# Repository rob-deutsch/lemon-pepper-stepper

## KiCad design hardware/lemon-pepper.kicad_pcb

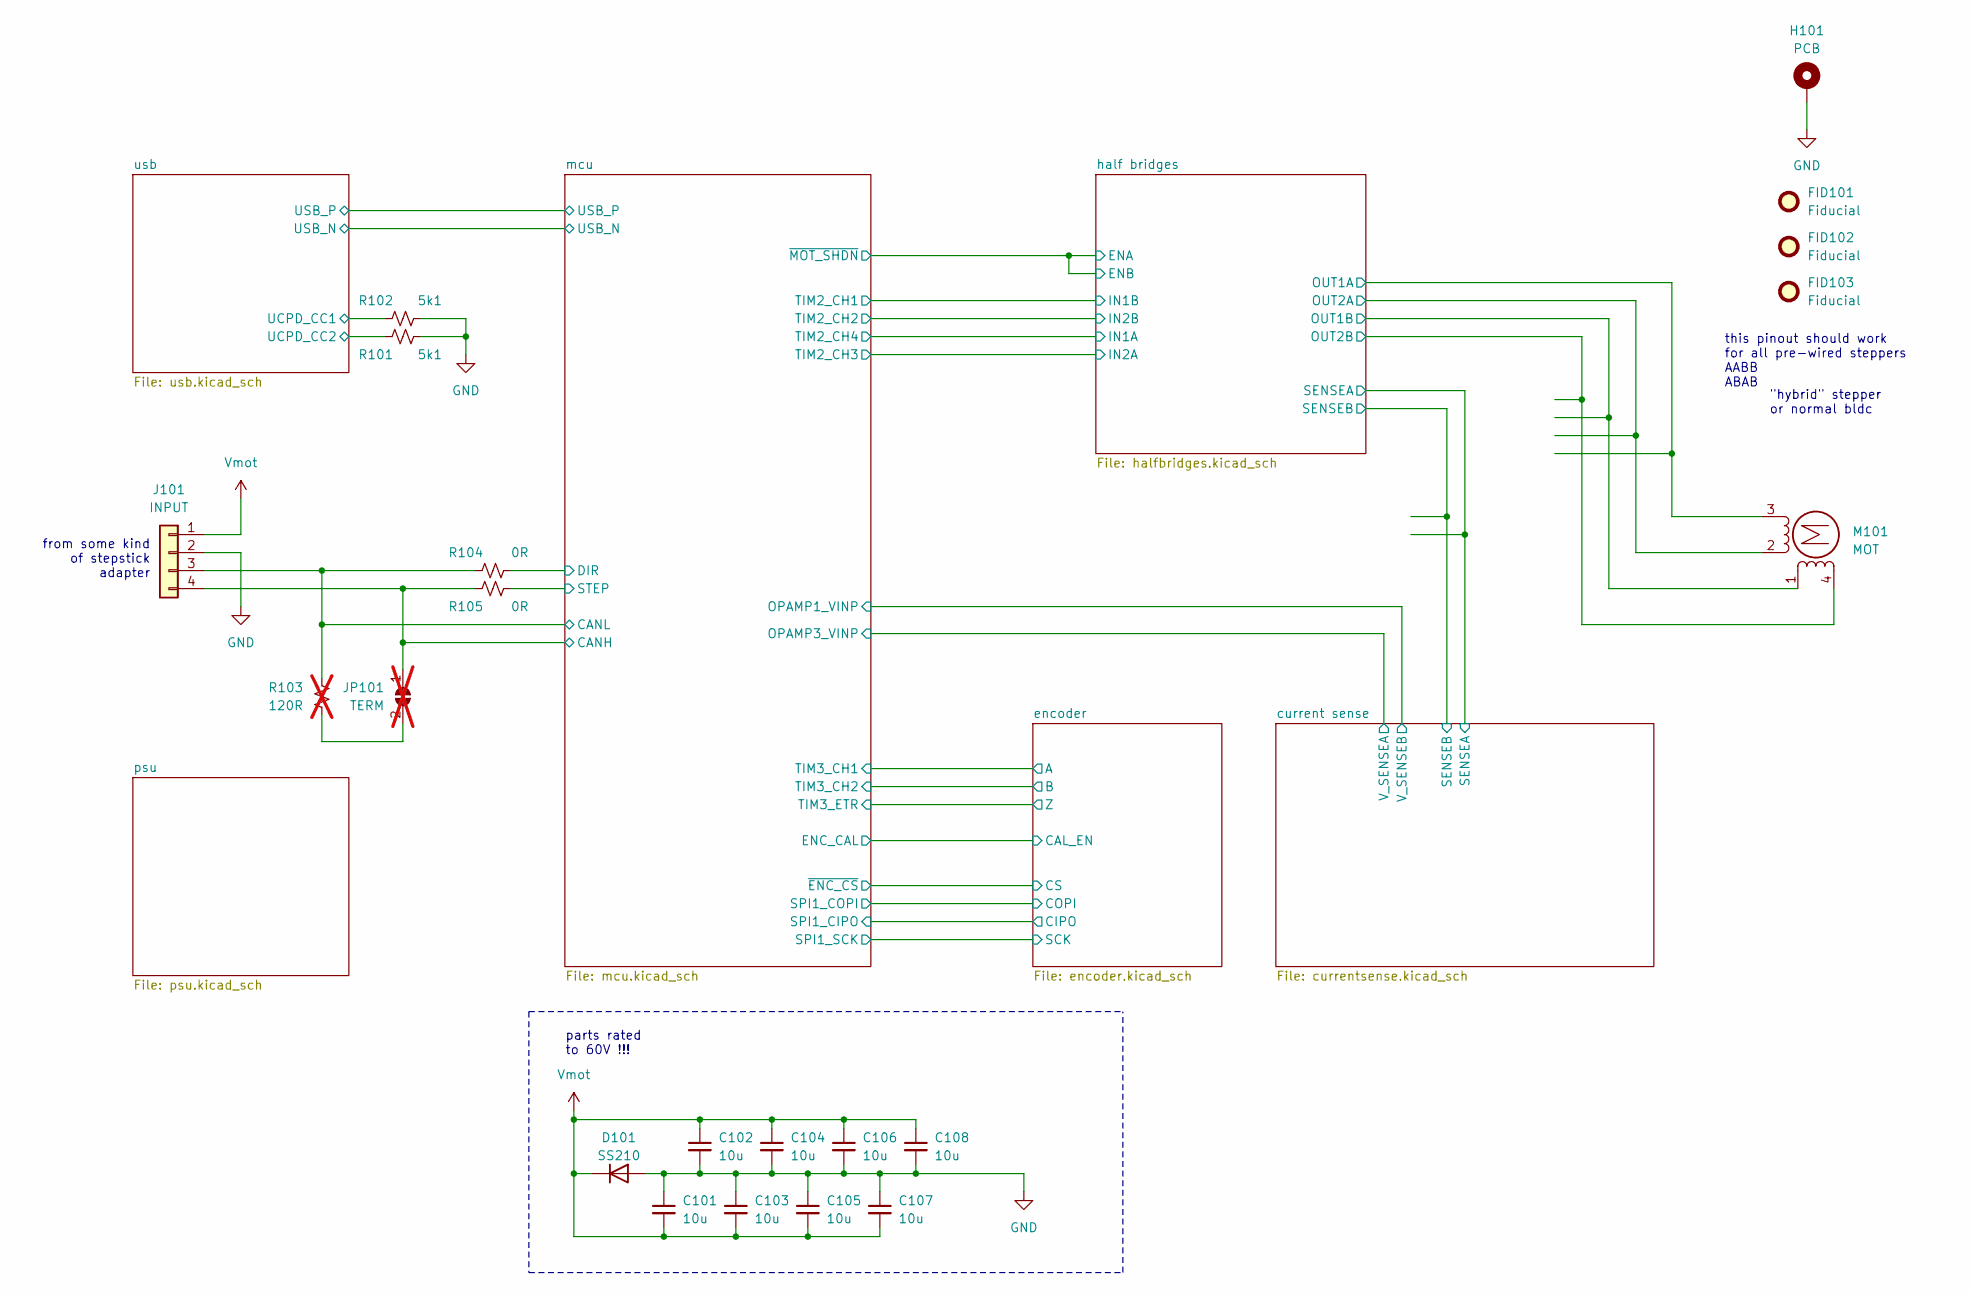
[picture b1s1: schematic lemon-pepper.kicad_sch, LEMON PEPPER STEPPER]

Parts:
C101, C102, C103, C104, C105, C106, C107, C108: 10u; C_0805_2012Metric; LCSC ID C440198
D101: SS210; D_SMA; LCSC ID C14996
FID101, FID102, FID103: Fiducial; Fiducial_0.5mm_Mask1mm
H101: PCB; NEMA17
J101: INPUT; JST_XH_B4B-XH-A_1x04_P2.50mm_Vertical
JP101: TERM; R_0402_1005Metric; not fitted
M101: MOT; XH2.54 4P
R101, R102: 5k1; R_0402_1005Metric; LCSC ID C25905
R103: 120R; R_0402_1005Metric; LCSC ID C25079; not fitted
R104, R105: 0R; R_0402_1005Metric; LCSC ID C17168

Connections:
/CANH: J101.4, JP101.1 (A), R105.2
/CANL: J101.3, R103.1, R104.1
/half bridges/OUT1A: M101.3; also elsewhere on the board
/half bridges/OUT1B: M101.1; also elsewhere on the board
/half bridges/OUT2A: M101.2 (-); also elsewhere on the board
/half bridges/OUT2B: M101.4; also elsewhere on the board
/mcu/DIR: R104.2; also elsewhere on the board
/mcu/STEP: R105.1; also elsewhere on the board
/usb/UCPD_CC1: R102.1; also elsewhere on the board
/usb/UCPD_CC2: R101.2; also elsewhere on the board
GND: C101.1, C102.2, C103.1, C104.2, C105.1, C106.2, C107.1, C108.2, D101.2 (A), H101.1, J101.2, R101.1, R102.2; also elsewhere on the board
unnamed: JP101.2 (B), R103.2
Vmot: C101.2, C102.1, C103.2, C104.1, C105.2, C106.1, C107.2, C108.1, D101.1 (K), J101.1; also elsewhere on the board

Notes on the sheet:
this pinout should work for all pre-wired steppers AABB ABAB
parts rated to 60V !!!
from some kind of stepstick adapter
"hybrid" stepper or normal bldc

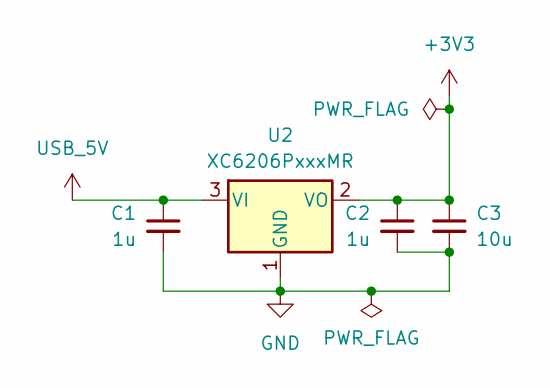
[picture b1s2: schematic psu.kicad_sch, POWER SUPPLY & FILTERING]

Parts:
C1, C2: 1u; C_0402_1005Metric; LCSC ID C52923
C3: 10u; C_0805_2012Metric; LCSC ID C440198
U2: XC6206PxxxMR; SOT-23-3; LCSC ID C5446

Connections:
+3V3: C2.1, C3.1, U2.2 (VO); also elsewhere on the board
GND: C1.2, C2.2, C3.2, U2.1 (GND); also elsewhere on the board
USB_5V: C1.1, U2.3 (VI); also elsewhere on the board

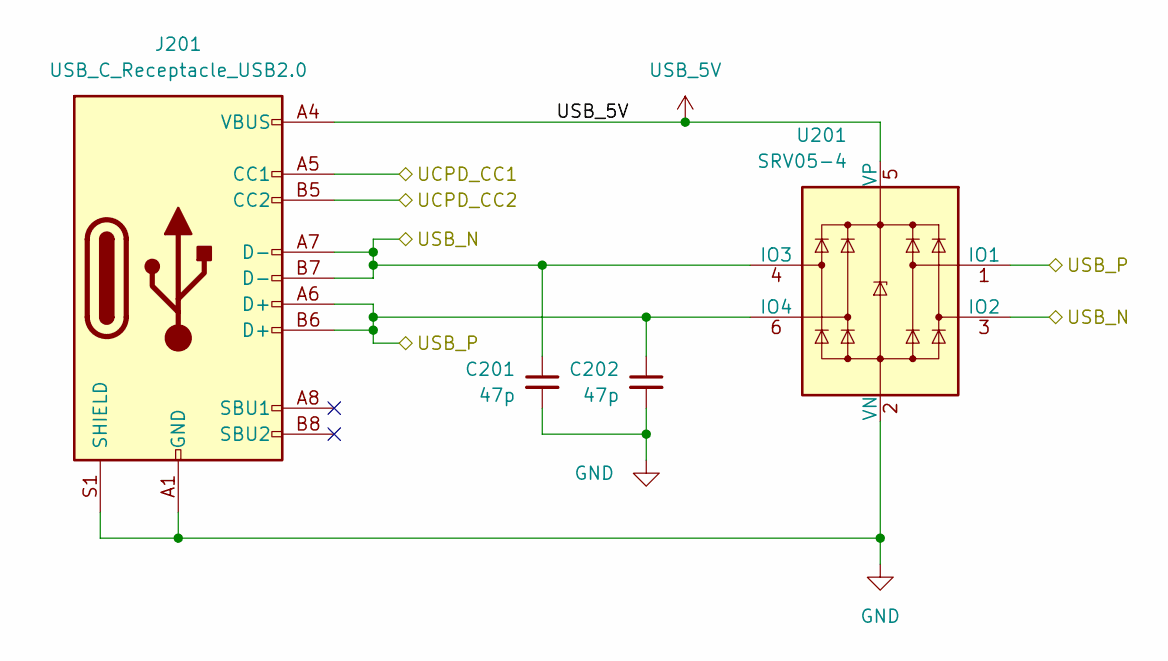
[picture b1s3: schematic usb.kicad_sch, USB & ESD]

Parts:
C201, C202: 47p; C_0402_1005Metric; LCSC ID C1567
J201: USB_C_Receptacle_USB2.0; usb_c; LCSC ID C963223
U201: SRV05-4; SOT-23-6; LCSC ID C7420376

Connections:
/mcu/USBD_N: C201.1, J201.A7 (D-), J201.B7 (D-), U201.3 (IO2), U201.4 (IO3); also elsewhere on the board
/mcu/USBD_P: C202.1, J201.A6 (D+), J201.B6 (D+), U201.1 (IO1), U201.6 (IO4); also elsewhere on the board
/usb/UCPD_CC1: J201.A5 (CC1); also elsewhere on the board
/usb/UCPD_CC2: J201.B5 (CC2); also elsewhere on the board
GND: C201.2, C202.2, J201.A1 (GND), J201.A12 (GND), J201.B1 (GND), J201.B12 (GND), J201.S1 (SHIELD), U201.2 (VN); also elsewhere on the board
USB_5V: J201.A4 (VBUS), J201.A9 (VBUS), J201.B4 (VBUS), J201.B9 (VBUS), U201.5 (VP); also elsewhere on the board

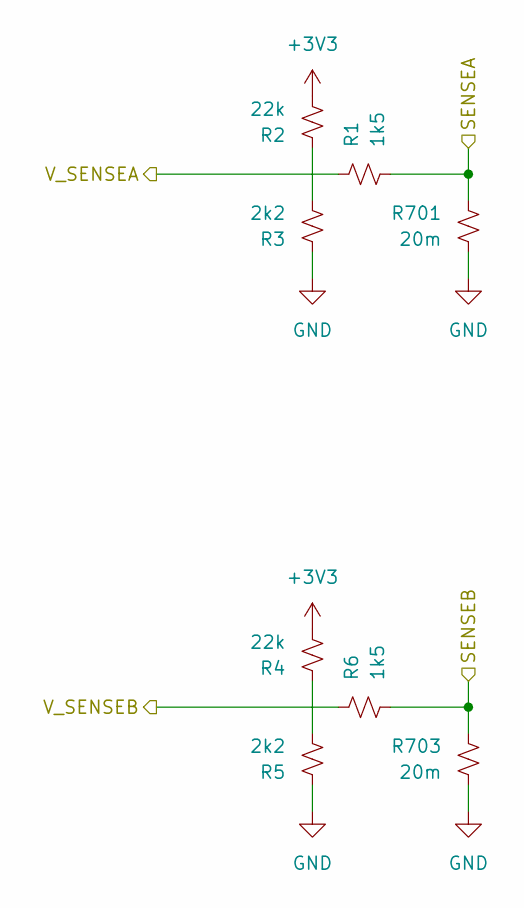
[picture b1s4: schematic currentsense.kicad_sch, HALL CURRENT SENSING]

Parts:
R1, R6: 1k5; R_0402_1005Metric; LCSC ID C25867
R2, R4: 22k; R_0402_1005Metric
R3, R5: 2k2; R_0402_1005Metric
R701, R703: 20m; R_1206_3216Metric; LCSC ID C393094

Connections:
+3V3: R2.2, R4.2; also elsewhere on the board
/current sense/SENSEA: R1.2, R701.1; also elsewhere on the board
/current sense/SENSEB: R6.2, R703.1; also elsewhere on the board
/current sense/V_SENSEA: R1.1; also elsewhere on the board
/current sense/V_SENSEB: R6.1; also elsewhere on the board
GND: R3.1, R5.1, R701.2, R703.2; also elsewhere on the board
unnamed: R2.1, R3.2
unnamed: R4.1, R5.2

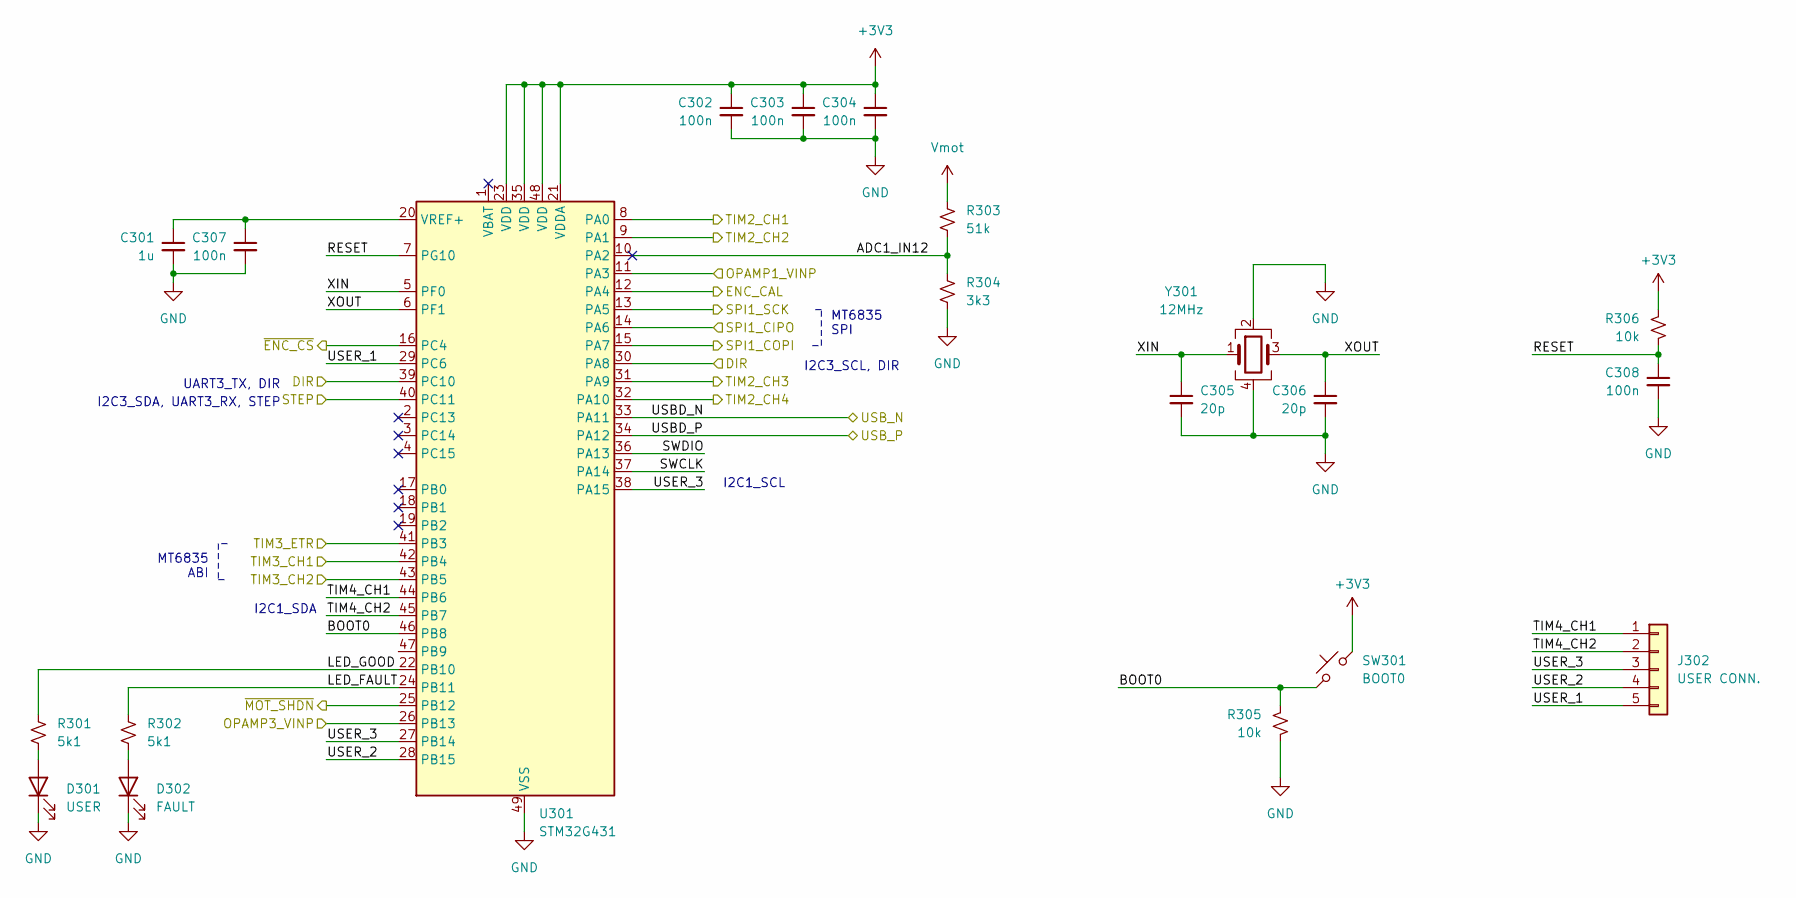
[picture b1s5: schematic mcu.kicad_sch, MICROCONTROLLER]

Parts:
C301: 1u; C_0402_1005Metric; LCSC ID C52923
C302, C303, C304, C307, C308: 100n; C_0402_1005Metric; LCSC ID C307331
C305, C306: 20p; C_0402_1005Metric; LCSC ID C1554
D301: USER; D_0603_1608Metric; LCSC ID C72041
D302: FAULT; D_0603_1608Metric; LCSC ID C2286
J302: USER CONN.; PinHeader_1x05_P1.27mm_SMD
R301, R302: 5k1; R_0402_1005Metric; LCSC ID C25905
R303: 51k; R_0402_1005Metric; LCSC ID C25794
R304: 3k3; R_0402_1005Metric; LCSC ID C25890
R305, R306: 10k; R_0402_1005Metric; LCSC ID C25744
SW301: BOOT0; SW_SPST_B3U-3000P; LCSC ID C963349
U301: STM32G431; QFN-48-1EP_7x7mm_P0.5mm_EP5.6x5.6mm; LCSC ID C529356
Y301: 12MHz; Crystal_SMD_3225-4Pin_3.2x2.5mm; LCSC ID C9002

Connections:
+3V3: C302.1, C303.1, C304.1, R306.1, SW301.2, U301.21 (VDDA), U301.23 (VDD), U301.35 (VDD), U301.48 (VDD); also elsewhere on the board
/current sense/V_SENSEA: U301.26 (PB13); also elsewhere on the board
/current sense/V_SENSEB: U301.11 (PA3); also elsewhere on the board
/encoder/A: U301.42 (PB4); also elsewhere on the board
/encoder/B: U301.43 (PB5); also elsewhere on the board
/encoder/CAL_EN: U301.12 (PA4); also elsewhere on the board
/encoder/CIPO: U301.14 (PA6); also elsewhere on the board
/encoder/COPI: U301.15 (PA7); also elsewhere on the board
/encoder/CS: U301.16 (PC4); also elsewhere on the board
/encoder/SCK: U301.13 (PA5); also elsewhere on the board
/encoder/Z: U301.41 (PB3); also elsewhere on the board
/half bridges/ENA: U301.25 (PB12); also elsewhere on the board
/half bridges/IN1A: U301.32 (PA10); also elsewhere on the board
/half bridges/IN1B: U301.8 (PA0); also elsewhere on the board
/half bridges/IN2A: U301.31 (PA9); also elsewhere on the board
/half bridges/IN2B: U301.9 (PA1); also elsewhere on the board
/mcu/ADC1_IN12: R303.2, R304.1, U301.10 (PA2)
/mcu/BOOT0: R305.1, SW301.1, U301.46 (PB8)
/mcu/DIR: U301.30 (PA8), U301.39 (PC10); also elsewhere on the board
/mcu/LED_FAULT: R302.1, U301.24 (PB11)
/mcu/LED_GOOD: R301.1, U301.22 (PB10)
/mcu/RESET: C308.1, R306.2, U301.7 (PG10); also elsewhere on the board
/mcu/STEP: U301.40 (PC11); also elsewhere on the board
/mcu/SWCLK: U301.37 (PA14); also elsewhere on the board
/mcu/SWDIO: U301.36 (PA13); also elsewhere on the board
/mcu/TIM4_CH1: J302.1, U301.44 (PB6)
/mcu/TIM4_CH2: J302.2, U301.45 (PB7)
/mcu/USBD_N: U301.33 (PA11); also elsewhere on the board
/mcu/USBD_P: U301.34 (PA12); also elsewhere on the board
/mcu/USER_1: J302.5, U301.29 (PC6)
/mcu/USER_2: J302.4, U301.28 (PB15)
/mcu/USER_3: J302.3, U301.27 (PB14), U301.38 (PA15)
/mcu/XIN: C305.1, U301.5 (PF0), Y301.1
/mcu/XOUT: C306.1, U301.6 (PF1), Y301.3
GND: C301.2, C302.2, C303.2, C304.2, C305.2, C306.2, C307.2, C308.2, D301.1 (K), D302.1 (K), R304.2, R305.2, U301.49 (VSS), Y301.2, Y301.4; also elsewhere on the board
unnamed: D301.2 (A), R301.2
unnamed: D302.2 (A), R302.2
unnamed: C301.1, C307.1, U301.20 (VREF+)
Vmot: R303.1; also elsewhere on the board

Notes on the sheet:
MT6835 ABI
I2C3_SDA, UART3_RX, STEP
I2C1_SDA
I2C1_SCL
MT6835 SPI
I2C3_SCL, DIR
UART3_TX, DIR

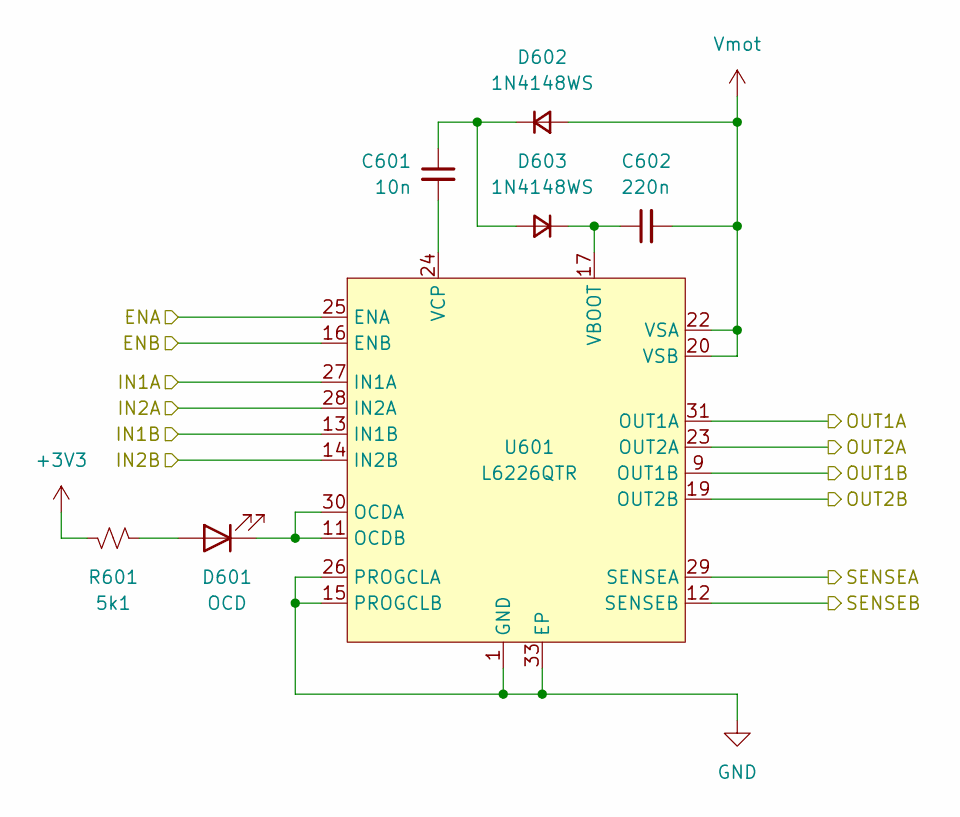
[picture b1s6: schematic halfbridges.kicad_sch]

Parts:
C601: 10n; C_0402_1005Metric; LCSC ID C15195
C602: 220n; C_0402_1005Metric; LCSC ID C16772
D601: OCD; D_0603_1608Metric; LCSC ID C2286
D602, D603: 1N4148WS; D_SOD-323; LCSC ID C81598
R601: 5k1; R_0402_1005Metric; LCSC ID C25905
U601: L6226QTR; ST-L6226Q-VQFN32; LCSC ID C95357

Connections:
+3V3: R601.2; also elsewhere on the board
/current sense/SENSEA: U601.29 (SENSEA); also elsewhere on the board
/current sense/SENSEB: U601.12 (SENSEB); also elsewhere on the board
/half bridges/ENA: U601.16 (ENB), U601.25 (ENA); also elsewhere on the board
/half bridges/IN1A: U601.27 (IN1A); also elsewhere on the board
/half bridges/IN1B: U601.13 (IN1B); also elsewhere on the board
/half bridges/IN2A: U601.28 (IN2A); also elsewhere on the board
/half bridges/IN2B: U601.14 (IN2B); also elsewhere on the board
/half bridges/OUT1A: U601.31 (OUT1A); also elsewhere on the board
/half bridges/OUT1B: U601.9 (OUT1B); also elsewhere on the board
/half bridges/OUT2A: U601.23 (OUT2A); also elsewhere on the board
/half bridges/OUT2B: U601.19 (OUT2B); also elsewhere on the board
GND: U601.1 (GND), U601.2 (NC), U601.3 (NC), U601.4 (NC), U601.5 (NC), U601.6 (NC), U601.7 (NC), U601.8 (NC), U601.15 (PROGCLB), U601.21 (GND), U601.26 (PROGCLA), U601.33 (EP); also elsewhere on the board
unnamed: D601.2 (A), R601.1
unnamed: D601.1 (K), U601.11 (OCDB), U601.30 (OCDA)
unnamed: C601.1, D602.1 (K), D603.2 (A)
unnamed: C602.1, D603.1 (K), U601.17 (VBOOT)
unnamed: C601.2, U601.24 (VCP)
Vmot: C602.2, D602.2 (A), U601.20 (VSB), U601.22 (VSA); also elsewhere on the board

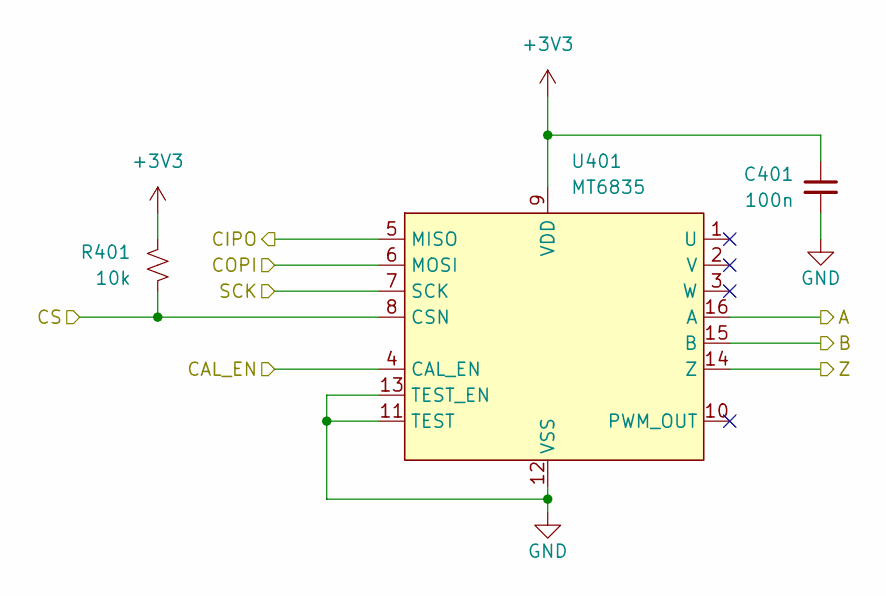
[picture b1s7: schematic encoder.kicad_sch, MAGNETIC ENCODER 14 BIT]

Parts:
C401: 100n; C_0402_1005Metric; LCSC ID C307331
R401: 10k; R_0402_1005Metric; LCSC ID C25744
U401: MT6835; MagnTek TSSOP-16-1EP_4.4x5mm_P0.65mm; LCSC ID C2932578

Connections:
+3V3: C401.1, R401.1, U401.9 (VDD); also elsewhere on the board
/encoder/A: U401.16 (A); also elsewhere on the board
/encoder/B: U401.15 (B); also elsewhere on the board
/encoder/CAL_EN: U401.4 (CAL_EN); also elsewhere on the board
/encoder/CIPO: U401.5 (MISO); also elsewhere on the board
/encoder/COPI: U401.6 (MOSI); also elsewhere on the board
/encoder/CS: R401.2, U401.8 (CSN); also elsewhere on the board
/encoder/SCK: U401.7 (SCK); also elsewhere on the board
/encoder/Z: U401.14 (Z); also elsewhere on the board
GND: C401.2, U401.11 (TEST), U401.12 (VSS), U401.13 (TEST_EN); also elsewhere on the board

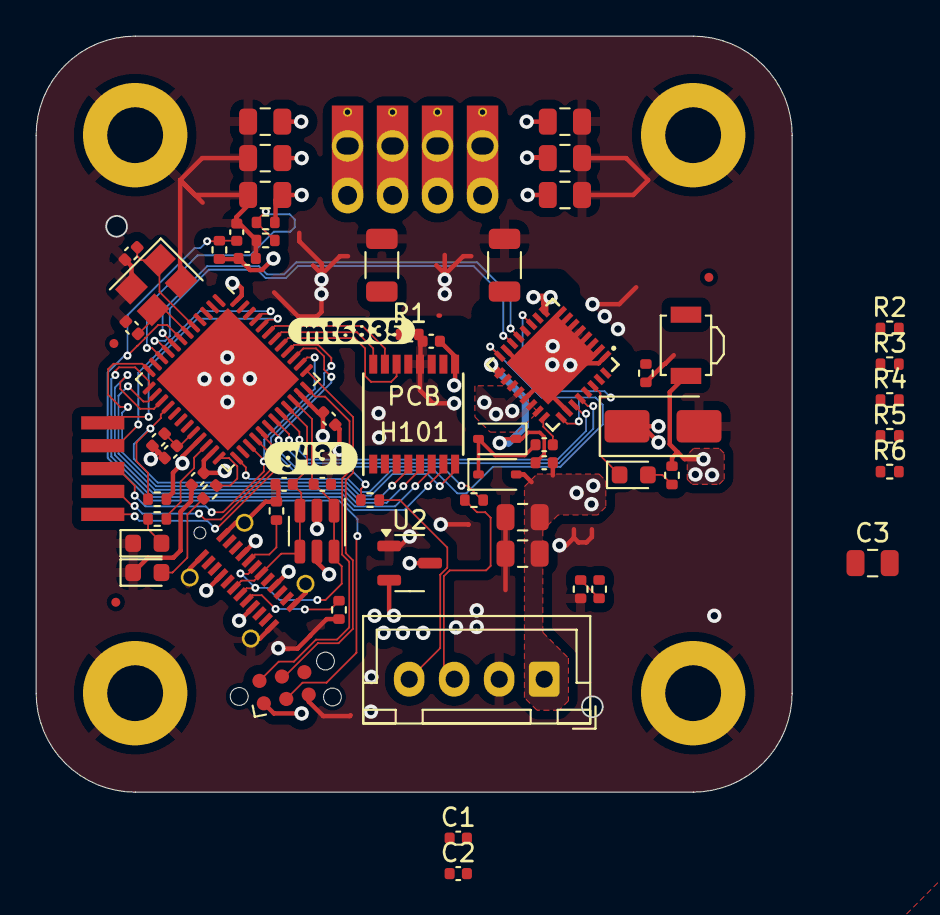
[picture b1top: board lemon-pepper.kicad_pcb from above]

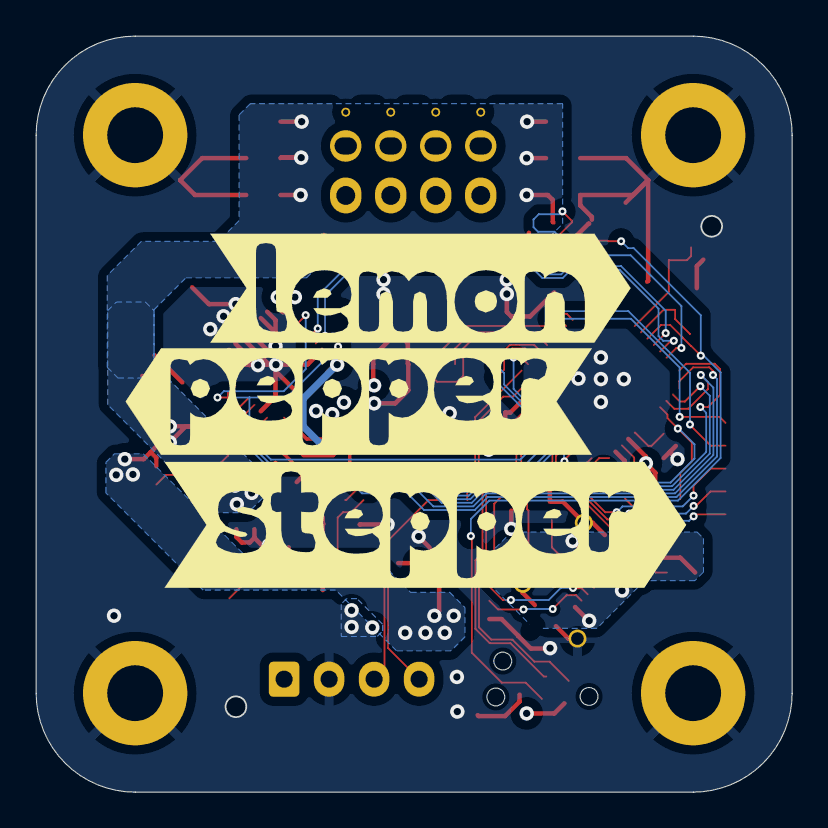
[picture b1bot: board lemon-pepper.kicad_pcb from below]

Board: 4 copper layers, 42.0 x 42.0 mm, 74 parts (3 on the bottom side), 58 nets.

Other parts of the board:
J301: TagConnect; Tag-Connect_TC2030-IDC-NL_2x03_P1.27mm_Vertical
R502: 51k; R_0402_1005Metric
R503: 22k; R_0402_1005Metric
kibuzzard-65A1D30A: G***; kibuzzard-65A1D30A
kibuzzard-652C57F7: G***; kibuzzard-652C57F7
kibuzzard-652C580D: G***; kibuzzard-652C580D
kibuzzard-6557D15D: G***; kibuzzard-6557D15D
kibuzzard-6557D149: G***; kibuzzard-6557D149
kibuzzard-6557D153: G***; kibuzzard-6557D153

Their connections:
+3V3: J301.1 (VCC); also elsewhere on the board
/mcu/RESET: J301.3 (~RESET); also elsewhere on the board
/mcu/SWCLK: J301.4 (SWCLK); also elsewhere on the board
/mcu/SWDIO: J301.2 (SWDIO); also elsewhere on the board
GND: J301.5 (GND), R503.2; also elsewhere on the board
unnamed: R502.2, R503.1

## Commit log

2024-06-06 first mod
2024-06-10 more mods
